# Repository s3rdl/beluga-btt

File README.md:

# Beluga Battery Temperature Tracking (BBTT)

ESPHome-based monitor for twelve independent NTC temperature channels.

## Hardware

- Three Olimex **ESP32-POE-ISO-EA** boards (ESP32-WROOM-32UE, 4 MB flash, external antenna), each with Ethernet/IEEE 802.3af PoE
- One Soldered ADS1115 module per Olimex board, connected to that board's UEXT I²C bus
- Both ADS1115 modules use address `0x48`; the address is reused because the boards have separate I²C buses
- I²C on each Olimex UEXT: SDA GPIO13, SCL GPIO16
- Four NTC channels per board, for twelve channels total
- Twelve independent dividers: `3.3 V → 10 kΩ fixed resistor → ADC node → NTC → GND`

See the [software guide](software/README.md), [wiring diagram](assets/battery-temperature-wiring.svg), and [KiCad carrier-board project](pcb/ADS1115/README.md). The KiCad design represents one node; use three identical carrier boards for the complete twelve-channel system.

The ordered Semitec **103JT-100** NTCs are specified as **10 kΩ at 25 °C** with a beta value of **3435 K**. The ESPHome configurations read the beta value from a local secret. The first Olimex node has been brought up and its readings are visible in Home Assistant; check the remaining nodes and all probes in the completed assembly.

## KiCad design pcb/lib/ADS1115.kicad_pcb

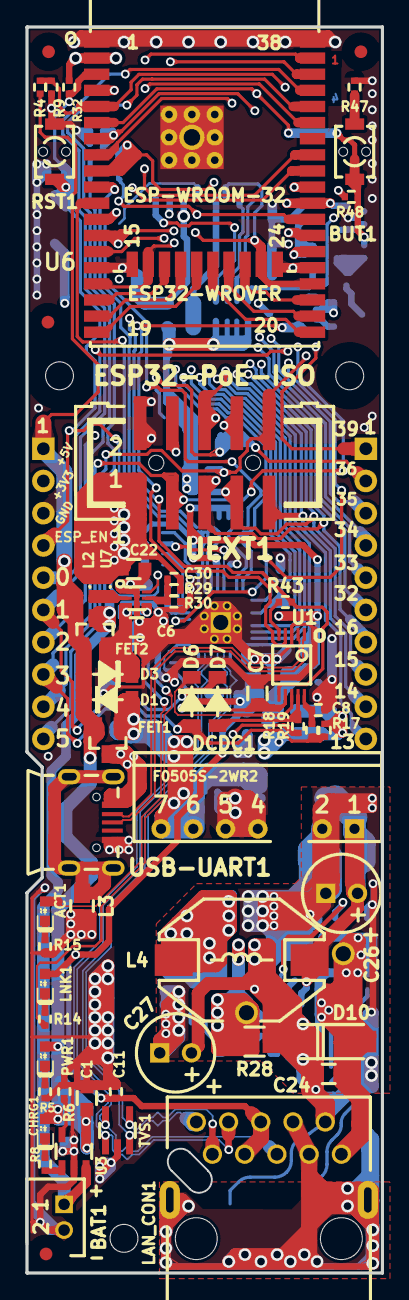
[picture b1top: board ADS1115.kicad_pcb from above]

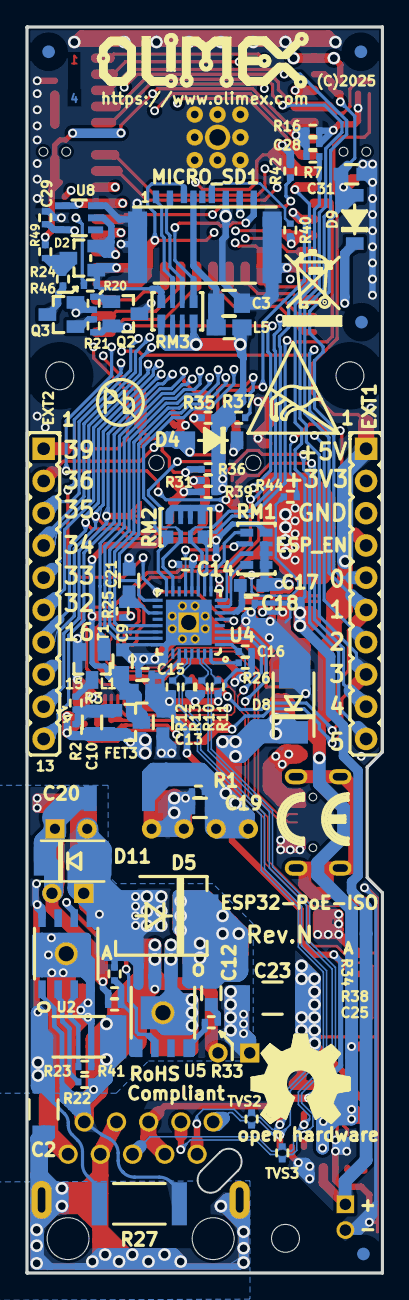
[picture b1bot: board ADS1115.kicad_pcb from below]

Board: 4 copper layers, 28.0 x 98.2 mm, 145 parts (84 on the bottom side), 95 nets.

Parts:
ACT1: LED/YELLOW/0603; LED_0603_KA
BAT1: DW02S; LIPO_BAT_VERTICAL_DW02S
BUT1: IT1185AU2; IT1185AU2_V2
C1, C6, C7, C9, C10, C13, C19, C22: 22uF/6.3V/20%/X5R/C0603; C_0603_5MIL_DWS
C2: 1nF/2000V/10%/X7R/C1206; C_1206_5MIL_DWS_ISO
C3: 47uF/6.3V/20%/X5R/C0805; C_0805_5MIL_DWS
C8, C11, C14, C15, C16, C18: 100nF/10V/20%/X5R/C0402; C_0402_5MIL_DWS
C12, C24: 100nF/100V/10%/X7R/C0603; C_0603_5MIL_DWS
C17: 2.2uF/6.3V/10%/X5R/C0603; C_0603_5MIL_DWS
C20: NA(1.0nF/3kV/10%/X7R/SMD/1808(VISHAY-VJ1808Y102KB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; C_1808(4520)_5MIL_DWS_ISO
C21: NA(10uF/6.3V/20%/X5R/C0603); C_0603_5MIL_DWS
C23: 1.0nF/3kV/10%/X7R/SMD/1808(VISHAY-VJ1808Y102KBHAT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; C_1808(4520)_5MIL_DWS_ISO
C25: 12pF/50V/5%/COG/C0402; C_0402_5MIL_DWS
C26: 470uF/10V/20%/Low_ESR/RM2.5/6.0x11mm; CPOL-RM2.5mm_6.3x11mm_PTH
C27: 15uF/100V/20%/RM2.5/6.3x11mm(Farnell:1281844); CPOL-RM2.5mm_6.3x11mm_PTH
C28: 1nF/50V/10%/X7R/C0402; C_0402_5MIL_DWS
C29: NA(100nF/10V/20%/X5R/C0402); C_0402_5MIL_DWS
C30: NA(120pF/50V/5%/C0G/C0402); C_0402_5MIL_DWS
C31: 1uF/10V/10%/X5R/C0603; C_0603_5MIL_DWS
CHRG1: LED/YELLOW/0603; LED_0603_KA
D1, D3, D4, D6, D7, D9: 1N5819S4/SOD123; SOD-123_1C-2A_KA
D2: BAT54C(SOT23-3); SOT23-3
D5: SS510/100V/5A/0.85V/DO214AB(SMC); DO214AB(SMC)_1(K)-2(A)
D8: NA(SMBJ6.0A); DO214AA_1(K)-2(A)
D10: SMAJ58A/SMA; SMA-KA
D11: SMBJ5.0A; DO214AA_1(K)-2(A)
DCDC1: F0505S-2WR2(SIP-7); SIP-7_Universal
Drill_Slot3: 2 mm; Mounting_hole_2_mm
EXT1, EXT2: NS(HN1x10); HN1x10
FET1, FET2, FET3: IRLML6402TRPbF; SOT23
FID1, FID4, FID7, FID8: Fiducial; Fiducial1x3_Paste
FID2, FID3, FID5, FID6: Fiducial; Fiducial1x3
L1, L3, L5: FB0805/600R/2A; L_0805_5MIL_DWS
L2: 1.0uH/4.2A/DCR=35mR/20%/2.00x1.60x1.00mm/L2016(PI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; L_2016_MM
L4: 33uH/2.1A/DCR=0.1R/20%/DBS135(PD3316MT330); DBS135
LAN_CON1: RJP-003TC1(LPJ4112CNL)
LNK1: LED/GREEN/0603; LED_0603_KA
Logo_OSHW: Sign_OSHW_8x8
Logo_Olimex: Logo_OLIMEX_TB
MH1, MH2, MH3: Mounting_Hole_NPTH; NPTH_2.2mm
MICRO_SD1: TFC-9P-1.7H(ATFFS150A01BR016); uSD(TFC-9P-1.xH(ATFFS150A01BR016))
PWR1: LED/RED/0603; LED_0603_KA
Q2, Q3: BC817-40(SOT23); SOT23
R1, R2, R6, R18, R19, R25, R32, R36, R37, R39, R48: 10k/R0402; R_0402_5MIL_DWS
R3, R20, R21: 1k/R0402; R_0402_5MIL_DWS
R4: 47k/R0402; R_0402_5MIL_DWS
R5, R8, R14, R15, R31, R35: 2.2k/R0402; R_0402_5MIL_DWS
R7, R16: 470k/R0402; R_0402_5MIL_DWS
R9: 100k/R0402; R_0402_5MIL_DWS
R10, R11, R12, R13: 49.9R/1%/R0402; R_0402_5MIL_DWS
R17, R49: NA/R0402; R_0402_5MIL_DWS
R22: 24.9k/1%/R0402; R_0402_5MIL_DWS
R23: 1.27k/1%/62.5mW/R0402; R_0402_5MIL_DWS
R24, R44, R46, R47: 220R/R0402; R_0402_5MIL_DWS
R26: 12.1k/1%/R0402; R_0402_5MIL_DWS
R27, R41: 9.1k/1W/R2512; R_2512_MM_DWS
R28: 0.03R/1%/R1206; R_1206_5MIL_DWS
R29: 220k/R0402; R_0402_5MIL_DWS
R30: 49.9k/1%/R0402; R_0402_5MIL_DWS
R33: 4.7R/R0402; R_0402_5MIL_DWS
R34: 10.5k/1%/R0402; R_0402_5MIL_DWS
R38: 56.2k/1%/R0402; R_0402_5MIL_DWS
R40: 10R/R0402; R_0402_5MIL_DWS
R42: NA(10R/R0402); R_0402_5MIL_DWS
R43: 4.7k/R0402; R_0402_5MIL_DWS
RM1, RM2, RM3: RA1206_(4X0603)_4B8_2.2k; R_MATRIX_4
RST1: IT1185AU2; IT1185AU2_V2
Sign_Antistatic: Val**; Sign_Antistatic
Sign_CE: CE_Sign
Sign_PB-Free: Sign_PB-Free
Sign_RecycleBin: Sign_RecycleBin_1
T1: LMUN2211LT1G(SOT-23); SOT23
TVS1: ESDS314DBVR(SOT-23-5); SOT-23-5
TVS2, TVS3: NA(GG0402052R542P); D_0402_5MIL_DWS
U1: CH340X(MSOP-10); MSOP-10_Pitch-0.5mm_3.00x3.00x1.00mm
U2: TPS2378DDAR(HSOIC-8); ESOIC-8
U3: TP4054-42-SOT25-R(SOT23-5); SOT-23-5
U4: LAN8710A-EZC(QFN32); QFN32_EP(33)_5.00x5.00x0.90mm_Pitch_0.50mm
U5: TX4138(ESOIC-8); ESOIC-8
U6: ESP32-WROOM-32E-N4; ESP32-WROVER_MODULE
U7: TPS62A02ADRLR(SOT-563-6); SOT-563-6
U8: NA(SN74LVC1G04DBVR(SOT23-5)); SOT-23-5
UEXT1: P-B-V-10-LF; GBH-254-SMT-10
USB-UART1: MISB-SWMM-5B-LF(USB_MICRO); USB-MICRO_MISB-SWMM-5B_LF

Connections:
+3.3V: C10.1, C22.1, C30.2, EXT1.2, FET3.2, L2.2, L5.1, R2.1, R17.1, R29.2, R31.1, R32.1, R35.1, R36.1, R37.1, R39.1, R48.1, RM3.1.2, RM3.2.2, RM3.3.2, RM3.4.2, U6.2 (VDD33(3V3)), UEXT1.1
+3.3VLAN: C9.1, C14.1, C29.2, FET3.3, L1.1, R25.2, RM1.4.1, RM2.1.1, RM2.2.1, RM2.3.1, RM2.4.1, U4.12 (VDDIO), U8.5 (VCC)
+5V: C1.1, CHRG1.2 (A), D1.1 (K), D3.2 (A), EXT1.1, FET1.2, FET2.1, PWR1.2 (A), R4.1, U3.4 (VCC)
+5VP: C19.1, C20.1, D1.2 (A), D8.1 (K), DCDC1.6 (Vout+), DCDC1.7 (Vout+), FET1.1, R1.1
/5V_DCDC: C20.2, C25.1, C26.1 (+), D11.1 (K), DCDC1.1 (Vin+), L4.2, R38.1
/+5V_USB: C7.1, FET1.3, R18.1, U1.7 (VCC), USB-UART1.1 (VBUS)
/D_Com: D2.3 (CC), R24.2, R49.2
/ESP_EN: C31.1, D9.2 (A), EXT1.4, R32.2, R44.2, RST1.1, U6.3 (EN)
/ETH_Shield: C2.2, LAN_CON1.0 (Shield), LAN_CON1.7 (GND/NC), LAN_CON1.8 (NC/GND)
/GPI34/BUT1: BUT1.1, EXT2.4, R48.2, R49.1, U6.6 (GPI34/ADC1_CH6/RTC_GPIO4)
/GPI35: C28.1, EXT2.3, R7.2, R16.1, U6.7 (GPI35/ADC1_CH7/RTC_GPIO5)
/GPI36/U1RXD: D4.2 (A), EXT2.2, R37.2, U6.4 (GPI36/SENSOR_VP/ADC1_CH0/RTC_GPIO0)
/GPI39: EXT2.1, R4.2, R9.1, U6.5 (GPI39/SENSOR_VN/ADC1_CH3/RTC_GPIO3)
/GPIO0: D2.2 (A2), EXT1.5, U6.25 (GPIO0/ADC2_CH1/TOUCH1/RTC_GPIO11/CLK_OU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), U8.2 (A)
/GPIO1/U0TXD: D7.1 (K), EXT1.6, U6.35 (GPIO1/U0TXD/CLK_OUT3/EMAC_RXD2)
/GPIO2/HS2_DATA0: D2.1 (A1), EXT1.7, R46.1, RM3.4.1, U6.24 (GPIO2/ADC2_CH2/TOUCH2/RTC_GPIO12/HSPIWP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), UEXT1.8
/GPIO3/U0RXD: D6.2 (A), EXT1.8, R17.2, R19.2, U6.34 (GPIO3/U0RXD/CLK_OUT2)
/GPIO4/U1TXD: EXT1.9, U6.26 (GPIO4/ADC2_CH0/TOUCH0/RTC_GPIO10/HSPIHD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), UEXT1.3
/GPIO5/SPI_CS: EXT1.10, R36.2, U6.29 (GPIO5/VSPICS0/HS1_DATA6/EMAC_RX_CLK), UEXT1.10
/GPIO12/PHY_PWR: T1.1 (B), U6.14 (GPIO12/ADC2_CH5/TOUCH5/RTC_GPIO15/MTDI/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)
/GPIO13/I2C-SDA: EXT2.10, R35.2, U6.16 (GPIO13/ADC2_CH4/TOUCH4/RTC_GPIO14/MTCK/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), UEXT1.6
/GPIO14/HS2_CLK: EXT2.9, R40.1, U6.13 (GPIO14/ADC2_CH6/TOUCH6/RTC_GPIO16/MTMS/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), UEXT1.9
/GPIO15/HS2_CMD: EXT2.8, MICRO_SD1.3 (CMD/DI), R39.2, U6.23 (GPIO15/ADC2_CH3/TOUCH3/MTDO/HSPICS0/RTC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), UEXT1.7
/GPIO16/I2C-SCL: EXT2.7, R31.2, R42.2, U6.27 (NC(GPIO16/HS1_DATA4/U2RXD/EMAC_CLK_OUT)), UEXT1.5
/GPIO17/EMAC_CLK_OUT_180: U4.5 (XTAL1/CLKIN), U6.28 (NC(GPIO17/HS1_DATA5/U2TXD/EMAC_CLK_OUT_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), U8.4 (Y)
/GPIO18/MDIO(RMII): RM2.4.2, U4.16 (MDIO), U6.30 (GPIO18/VSPICLK/HS1_DATA7)
/GPIO19/EMAC_TXD0(RMII): U4.22 (TXD0), U6.31 (GPIO19/VSPIQ/U0CTS/EMAC_TXD0)
/GPIO21/EMAC_TX_EN(RMII): U4.21 (TXEN), U6.33 (GPIO21/VSPIHD/EMAC_TX_EN)
/GPIO22/EMAC_TXD1(RMII): U4.23 (TXD1), U6.36 (GPIO22/VSPIWP/U0RTS/EMAC_TXD1)
/GPIO23/MDC(RMII): U4.17 (MDC), U6.37 (GPIO23/VSPID/HS1_STROBE)
/GPIO25/EMAC_RXD0(RMII): RM2.2.2, U4.11 (RXD0/MODE0), U6.10 (GPIO25/DAC_1/ADC2_CH8/RTC_GPIO6/EMAC_RX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)
/GPIO26/EMAC_RXD1(RMII): RM2.1.2, U4.10 (RXD1/MODE1), U6.11 (GPIO26/DAC_2/ADC2_CH9/RTC_GPIO7/EMAC_RX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)
/GPIO27/EMAC_RX_CRS_DV: RM2.3.2, U4.15 (COL/CRS_DV/MODE2), U6.12 (GPIO27/ADC2_CH7/TOUCH7/RTC_GPIO17/EMAC_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)
/GPIO32: EXT2.6, U6.8 (GPIO32/XTAL_32K_P/ADC1_CH4/TOUCH9/RTC_G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)
/GPIO33: EXT2.5, R42.1, U6.9 (GPIO33/XTAL_32K_N/ADC1_CH5/TOUCH8/RTC_G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)
/ILIM: R28.1, U5.2 (ILIM), U5.9 (ILIM)
/PG: R44.1, U7.6 (PG)
/RD+: LAN_CON1.3 (RD+), R11.2, TVS1.1 (I/O1), TVS3.2 (IO2), U4.31 (RXP)
/RD-: LAN_CON1.6 (RD-), R10.2, TVS1.5 (I/O4), TVS3.1 (IO1), U4.30 (RXN)
/TD+: LAN_CON1.1 (TD+), R13.2, TVS1.3 (I/O2), TVS2.2 (IO2), U4.29 (TXP)
/TD-: LAN_CON1.2 (TD-), R12.2, TVS1.4 (I/O3), TVS2.1 (IO1), U4.28 (TXN)
/USB_D+: U1.1 (UD+), USB-UART1.3 (D+)
/USB_D-: U1.2 (UD-), USB-UART1.2 (D-)
Earth: C2.1, C23.2, C26.2 (-), C27.2 (-), D5.2 (A), D11.2 (A), DCDC1.2 (Vin-), R27.2, R34.2, R41.2, U2.5 (RTN), U2.8 (APD), U5.4 (GND)
GND: BAT1.2, C1.2, C3.2, C6.2, C7.2, C8.2, C9.2, C11.2, C13.2, C14.2, C15.2, C16.2, C17.2, C18.2, C19.2, C21.1, C22.2, C23.1, C28.2, C29.1, C31.2, D8.2 (A), DCDC1.4 (Vout-), DCDC1.5 (Vout-), EXT1.3, L3.2, MICRO_SD1.6 (GND), MICRO_SD1.CH1 (Card_Housing), R1.2, R5.2, R6.2, R9.2, R15.2, R16.2, R26.2, R30.2, R47.2, RM1.1.1, RM1.2.1, RM1.3.1, RST1.2, T1.2 (E), TVS1.2 (GND), U1.3 (GND), U3.2 (GND), U4.24 (TXD2), U4.25 (TXD3), U4.33 (GND), U6.1 (GND), U6.15 (GND), U6.38 (GND), U6.39 (THERMAL_PAD), U7.1 (GND), U8.3 (GND), UEXT1.2, USB-UART1.5 (GND)
unnamed: ACT1.2 (A), U4.3 (LED1/REGOFF)
unnamed: ACT1.1 (K), R15.1
unnamed: BUT1.2, R47.1
unnamed: C10.2, FET3.1, R2.2, R3.1
unnamed: C12.2, R33.2
unnamed: CHRG1.1 (K), R8.1
unnamed: C6.1, D3.1 (K), FET2.2, U7.3 (VIN), U7.4 (EN)
unnamed: D4.1 (K), UEXT1.4
unnamed: C12.1, D5.1 (K), L4.1, U5.1 (SW)
unnamed: D6.1 (K), U1.8 (TXD)
unnamed: D7.2 (A), R18.2, U1.9 (RXD)
unnamed: D9.1 (K), Q2.3 (C)
unnamed: L3.1, USB-UART1.0
unnamed: C11.1, C13.1, C15.1, C16.1, L1.2, LAN_CON1.4 (TCT), LAN_CON1.5 (RCT), LNK1.2 (A), R10.1, R11.1, R12.1, R13.1, U4.1 (VDD2A), U4.27 (VDD1A)
unnamed: LNK1.1 (K), R14.1
unnamed: MICRO_SD1.2 (CD/DAT3/CS), RM3.2.1
unnamed: MICRO_SD1.5 (CLK/SCLK), R40.2
unnamed: MICRO_SD1.7 (DAT0/DO), R46.2
unnamed: MICRO_SD1.8 (DAT1/RES), RM3.1.1
unnamed: MICRO_SD1.1 (DAT2/RES), RM3.3.1
unnamed: C3.1, L5.2, MICRO_SD1.4 (VDD)
unnamed: PWR1.1 (K), R5.1
unnamed: Q2.1 (B), R20.2
unnamed: Q2.2 (E), R21.1, U1.4 (RTS#)
unnamed: Q3.1 (B), R21.2
unnamed: Q3.3 (C), R24.1
unnamed: Q3.2 (E), R20.1, R43.1, U1.6 (TNOW/DTR#)
unnamed: R3.2, T1.3 (C)
unnamed: R43.2, U1.5 (CTS#)
unnamed: C8.1, R19.1, U1.10 (V3)
unnamed: U2.6 (CDB), U5.6 (EN)
unnamed: R23.1, U2.3 (CLS)
unnamed: R22.2, U2.2 (DEN)
unnamed: R8.2, U3.1 (CHRGb)
unnamed: R6.1, U3.5 (PROG)
unnamed: BAT1.1, FET2.3, R7.1, U3.3 (VBAT)
unnamed: R14.2, U4.2 (LED2/NINTSEL)
unnamed: C21.2, R25.1, U4.19 (NRST)
unnamed: R26.1, U4.32 (RBIAS)
unnamed: RM1.1.2, U4.7 (RXCLK/PHYAD1)
unnamed: RM1.4.2, U4.9 (RXD2/RMIISEL)
unnamed: RM1.2.2, U4.8 (RXD3/PHYAD2)
unnamed: RM1.3.2, U4.13 (RXER/RXD4/PHYAD0)
unnamed: C17.1, C18.1, U4.6 (VDDCR)
unnamed: R33.1, U5.8 (BS)
unnamed: C25.2, R34.1, R38.2, U5.5 (FB)
unnamed: C30.1, R29.1, R30.1, U7.5 (FB)
unnamed: L2.1, U7.2 (SW)
Spare1: C24.1, C27.1 (+), D10.1 (K), LAN_CON1.9 (PW+), R22.1, R27.1, R28.2, R41.1, U2.1 (VDD), U5.3 (Vin)
Spare2: C24.2, D10.2 (A), LAN_CON1.10 (PW-), R23.2, U2.4 (VSS), U2.9 (EPAD)

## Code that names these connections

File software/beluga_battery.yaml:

substitutions:
  name: beluga-battery
  friendly_name: Beluga Battery

esphome:
  name: ${name}
  name_add_mac_suffix: false
  friendly_name: ${friendly_name}

esp32:
  board: esp32-poe-iso
  variant: esp32
  framework:
    type: esp-idf

logger:

api:

ota:
  - platform: esphome

ethernet:
  type: LAN8720
  mdc_pin: GPIO23
  mdio_pin: GPIO18
  clk:
    pin: GPIO17
    mode: CLK_OUT
  phy_addr: 0
  power_pin:
    number: GPIO12
    ignore_strapping_warning: true

i2c:
  sda: GPIO13
  scl: GPIO16
  scan: true

# This board has its own I²C bus; its ADS1115 address can therefore be 0x48.
ads1115:
  - id: ads1115_0x48
    address: 0x48

# Divider per channel: 3.3 V -> fixed 10 kΩ -> ADC node -> NTC -> GND.
# NTC: Semitec 103JT-100, 10 kΩ at 25 °C, beta 3435 K (datasheet).
# Supply the NTC beta value through ntc_beta_k in the local secrets.yaml.
sensor:
  - platform: ads1115
    ads1115_id: ads1115_0x48
    multiplexer: A0_GND
    gain: 4.096
    name: "Beluga NTC 1 Voltage"
    id: ntc1_voltage
    update_interval: 5s


  - platform: resistance
    sensor: ntc1_voltage
    configuration: DOWNSTREAM
    resistor: 10kOhm
    name: "Beluga NTC 1 Resistance"
    id: ntc1_resistance


  - platform: ntc
    sensor: ntc1_resistance
    name: "Beluga NTC 1 Temperature"
    calibration:
      b_constant: !secret ntc_beta_k
      reference_temperature: 25°C
      reference_resistance: 10kOhm


  - platform: ads1115
    ads1115_id: ads1115_0x48
    multiplexer: A1_GND
    gain: 4.096
    name: "Beluga NTC 2 Voltage"
    id: ntc2_voltage
    update_interval: 5s


  - platform: resistance
    sensor: ntc2_voltage
    configuration: DOWNSTREAM
    resistor: 10kOhm
    name: "Beluga NTC 2 Resistance"
    id: ntc2_resistance


  - platform: ntc
    sensor: ntc2_resistance
    name: "Beluga NTC 2 Temperature"
    calibration:
      b_constant: !secret ntc_beta_k
      reference_temperature: 25°C
      reference_resistance: 10kOhm


  - platform: ads1115
    ads1115_id: ads1115_0x48
    multiplexer: A2_GND
    gain: 4.096
    name: "Beluga NTC 3 Voltage"
    id: ntc3_voltage
    update_interval: 5s


  - platform: resistance
    sensor: ntc3_voltage
    configuration: DOWNSTREAM
    resistor: 10kOhm
    name: "Beluga NTC 3 Resistance"
    id: ntc3_resistance


  - platform: ntc
    sensor: ntc3_resistance
    name: "Beluga NTC 3 Temperature"
    calibration:
      b_constant: !secret ntc_beta_k
      reference_temperature: 25°C
      reference_resistance: 10kOhm


  - platform: ads1115
    ads1115_id: ads1115_0x48
    multiplexer: A3_GND
    gain: 4.096
    name: "Beluga NTC 4 Voltage"
    id: ntc4_voltage
    update_interval: 5s


  - platform: resistance
    sensor: ntc4_voltage
    configuration: DOWNSTREAM
    resistor: 10kOhm
    name: "Beluga NTC 4 Resistance"
    id: ntc4_resistance


  - platform: ntc
    sensor: ntc4_resistance
    name: "Beluga NTC 4 Temperature"
    calibration:
      b_constant: !secret ntc_beta_k
      reference_temperature: 25°C
      reference_resistance: 10kOhm

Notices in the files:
pcb/lib/ADS1115.kicad_pcb:
(C)2025
